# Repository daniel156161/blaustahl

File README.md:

# Blaustahl Storage Device

The Blaustahl USB dongle provides long-term storage for about 8000 characters of text. Simply plug the device into your computer and open any serial communications program that supports VT100 emulation (PuTTY, Tera Term, Minicom, screen, etc.) in order to access the built-in text editor.

This repo contains schematics, PCB layouts, firmware and a 3D-printable case.

Find usage instructions and more information on the [Blaustahl product page](https://machdyne.com/product/blaustahl-storage-device/).

## Connecting Blaustahl

The following sections will describe how to connect to Blaustahl on different operating systems. Once you're connected, press CTRL-G to view the on-device help screen.

### Linux

1. Install screen or minicom:

```
$ sudo apt install screen
$ sudo apt install minicom
```

2. After plugging in Blaustahl, find the device:

```
$ dmesg | grep ACM
```

3. Connect to the device (for example):

```
$ screen /dev/ttyACM0
or
$ minicom -D /dev/ttyACM0
```

If the device is already plugged in and you see nothing, you may need to press CTRL-L to refresh the display.

### OS X

1. Open the Terminal application.

2. After plugging in Blaustahl, find the device:

```
$ ls /dev/tty.usbmodem*
```

3. Connect to the device (for example):

```
$ screen /dev/tty.usbmodem1234561
```

### Windows

1. Download and install [PuTTY](https://www.chiark.greenend.org.uk/~sgtatham/putty/latest.html).

2. After plugging in Blaustahl, find the device by opening Device Manager and looking under "Ports (COM & LPT)" for "USB Serial Device (COMx)".

3. Open PuTTY and set connection type to Serial. Enter COMx (e.g. COM4) in the serial line box and press the Open button.

### Nix Flake Support

For users who prefer Nix, a [Nix Flake](https://nixos.wiki/wiki/Flakes) is now available to simplify building and using Blaustahl's firmware and utility tools. This section offers an alternative method that does not replace the existing instructions for non-Nix environments.

#### Prerequisites:
- Install [Nix](https://nixos.org/download) and enable flake support by adding `experimental-features = nix-command flakes` to your Nix configuration.

#### Building with the Flake:

Instead of cloning the repository manually, you can reference the flake directly using its GitHub address.

1. Use the flake to build the firmware, `bs` utility, or `srwp` tool:

    - To build and obtain the firmware files:
      ```bash
      nix build github:machdyne/blaustahl#firmware
      ```
      The UF2 files will be placed in `result/lib/firmware/`.

    - To build the `bs` utility:
      ```bash
      nix build github:machdyne/blaustahl#bs
      ```
      The binary will be available in the Nix store, with a symlink at `result/bin/bs`.

    - To build the `srwp` tool:
      ```bash
      nix build github:machdyne/blaustahl#srwp
      ```
      Similarly, you'll find the resulting script or binary under `result/bin/srwp`.

**Note:**
- These steps are optional for those using Nix and do not affect the regular installation and usage instructions provided above for other environments.

## Using Blaustahl

Blaustahl includes a built-in text editor with four 80x24 pages of text. The cursor can be moved with the arrow keys. When you'd like to enter or delete text, press CTRL-W to toggle the write mode.

| Keypress | Action |
| -------- | ------ |
| CTRL-G | Help |
| CTRL-L | Refresh screen |
| CTRL-W | Toggle write mode |
| CTRL-S | Toggle status bar |
| CTRL-Y | Enter firmware update mode |
| PGUP/DN | Navigate between pages |
| CTRL-A or ^ | Move to beginning of line |
| CTRL-E or $ | Move to end of line |

## Software

The 'bs' utility program can be used to read and write the FRAM data. Note that it's not possible to use this utility with the cdconly firmware, please install the composite firmware (blaustahl-x.x.x.uf2) in order to use the `bs` utility.

Build and install:

If using OS X:
```
$ brew install libusb
```

If using Linux:
```
$ sudo apt install libusb-1.0-0-dev
```

Then:

```
$ cd sw
$ make
$ sudo make install
$ sudo bs -r my-backup.bin
```
## API

To read or write data to FRAM memory via software, use the built-in API Simple Read Write Protocol (SRWP). An example and description of the protocol can be found in this [repository](https://github.com/binqbit/serialport_srwp).

See `sw/srwp.py` for an SRWP example using Python.

## Firmware

The [firmware](firmware) can be updated over USB by pressing CTRL-Y in the text editor to enter the UF2 bootloader mode. You can also enter the bootloader by holding the button while plugging in the device.

Once in bootloader mode, you can update the firmware by dragging and dropping a new UF2 file to the device.

There are two firmware images available:

  * blaustahl-x.x.x.uf2: USB composite device with USB-CDC and vendor interface
  * blaustahl\_cdconly-x.x.x.uf2: USB-CDC simple device

Blaustahl ships with `ship/blaustahl\_cdconly.uf2` installed.

The vendor interface allows you to access the 'bs' utility and to develop custom
software that interfaces with Blaustahl.

You can build the firmware from source, if you have [pico-sdk](https://github.com/raspberrypi/pico-sdk) installed:

```
$ cd firmware/blaustahl
$ mkdir build
$ cd build
$ cmake ..
$ make
```

## Future data recovery

In the event that the USB interface were to become obsolete or the RP2040 were to become non-functional, it should still be possible to recover the FRAM data using a SOP-8 test clip. The FRAM IC is marked "RS64".

One way to achieve this today is to load the Blaustahl firmware onto a Raspberry Pi Pico using the same SPI GPIOs as shown in the schematics, then hold the Blaustahl boot button while attaching a test clip to the FRAM IC. The text editor or 'bs' utility can then be used to recover the FRAM data.

## License

The contents of this repo are released under the [Lone Dynamics Open License](LICENSE.md).

Note: You can use these designs for commercial purposes but we ask that instead of producing exact clones, that you either replace our trademarks and logos with your own or add your own next to ours.

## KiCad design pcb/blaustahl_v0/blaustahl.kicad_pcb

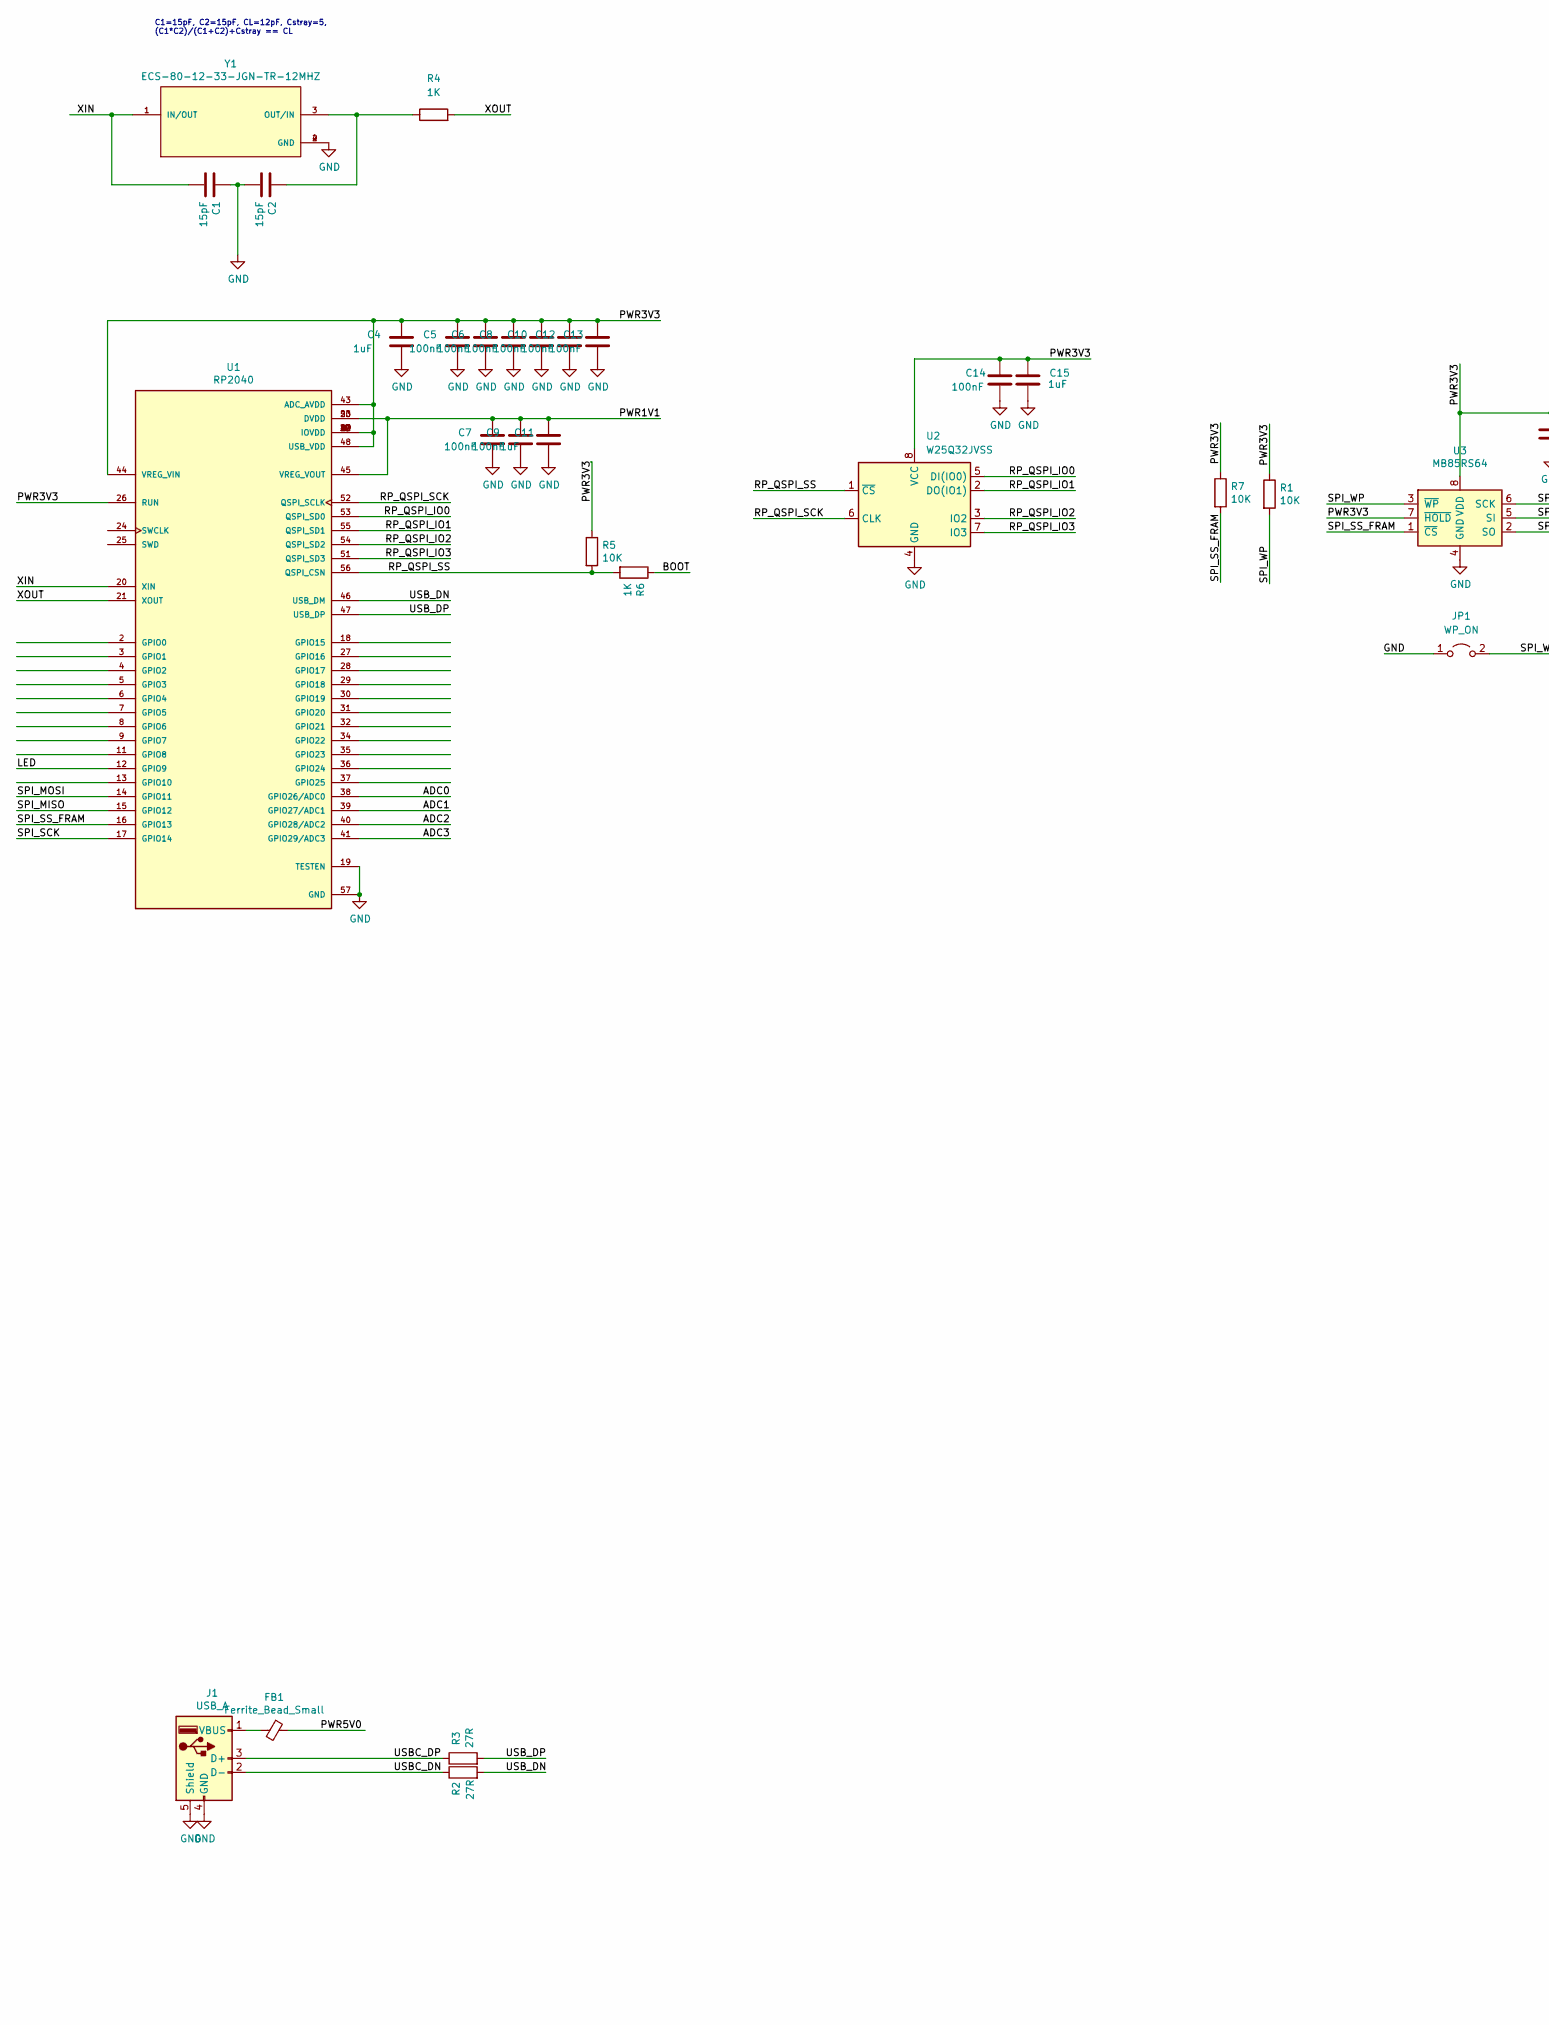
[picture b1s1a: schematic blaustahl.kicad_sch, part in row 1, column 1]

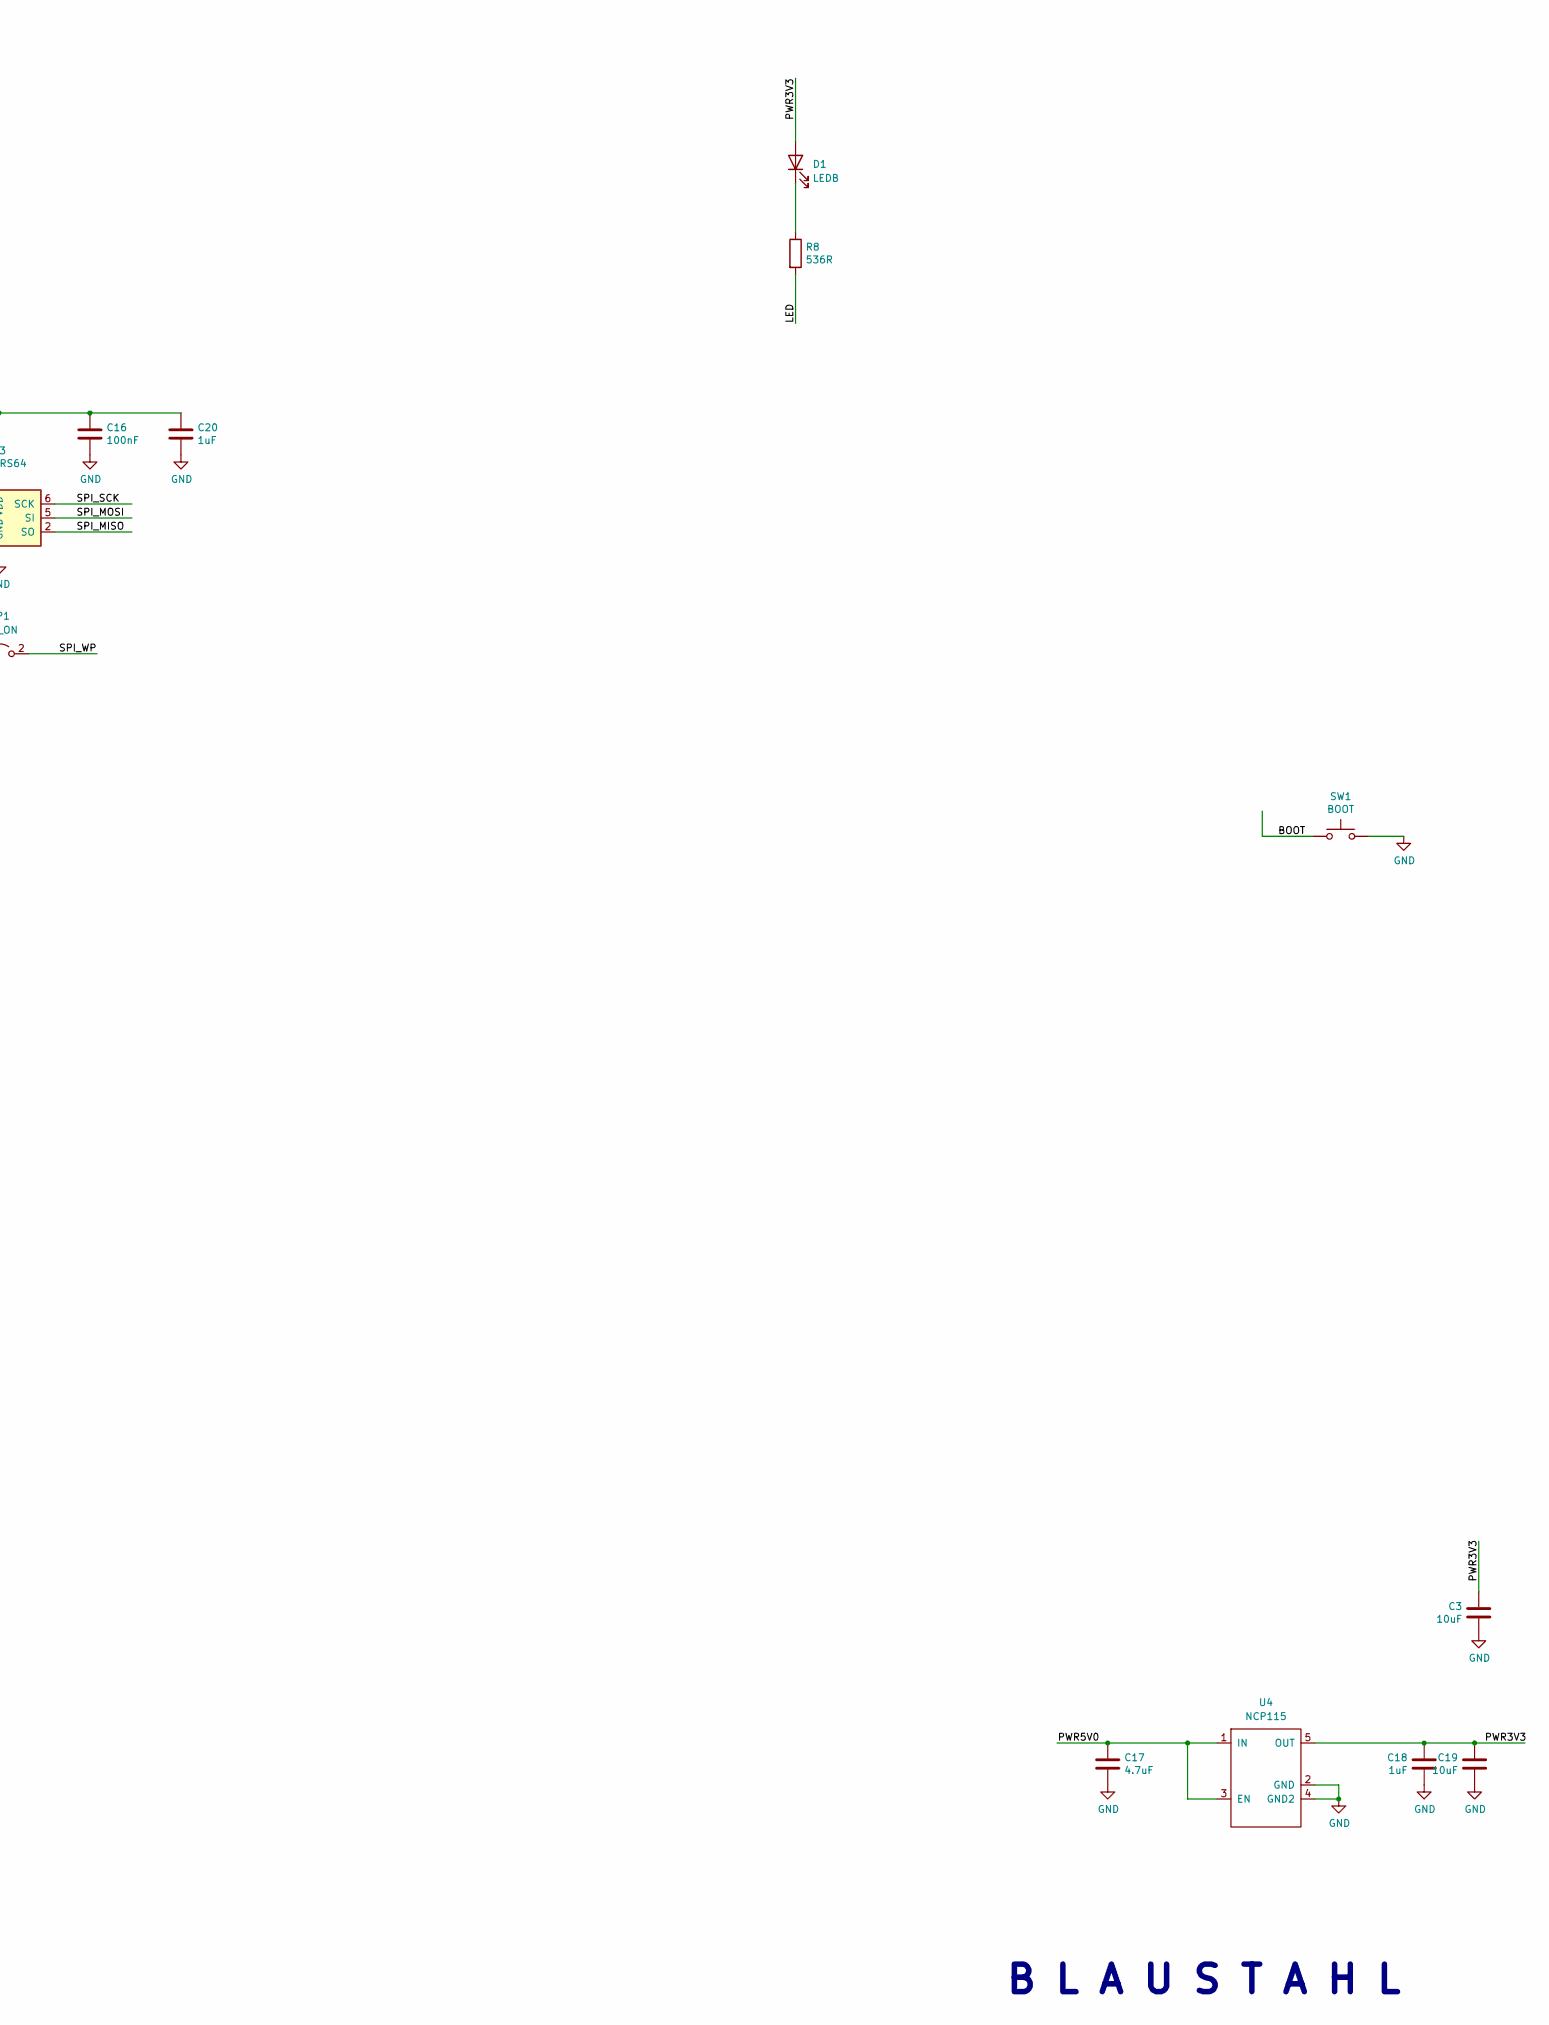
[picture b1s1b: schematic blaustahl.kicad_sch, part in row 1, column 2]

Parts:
C1, C2: 15pF; C_0402_1005Metric
C3, C19: 10uF; C_0402_1005Metric
C4, C11, C15, C18, C20: 1uF; C_0402_1005Metric
C5, C6, C7, C8, C9, C10, C12, C13, C14, C16: 100nF; C_0402_1005Metric
C17: 4.7uF; C_0402_1005Metric
D1: LEDB; LED_0603_1608Metric
FB1: Ferrite_Bead_Small; R_0402_1005Metric
J1: USB_A; USB_A_CNCTech_1001-011-01101_Horizontal
JP1: WP_ON; SolderJumper-2_P1.3mm_Open_Pad1.0x1.5mm
R1, R5, R7: 10K; R_0402_1005Metric
R2, R3: 27R; R_0402_1005Metric
R4, R6: 1K; R_0402_1005Metric
R8: 536R; R_0402_1005Metric
SW1: BOOT; Button_2P_3x4mm
U1: RP2040; RP2040-QFN-56-OFFICIAL; PARTREV 1.6.1
U2: W25Q32JVSS; SOIC-8_3.9x4.9mm_P1.27mm
U3: MB85RS64; SOIC-8_3.9x4.9mm_P1.27mm
U4: NCP115; TSOP-5_1.65x3.05mm_P0.95mm
Y1: ECS-80-12-33-JGN-TR-12MHZ; XTAL_ECS-240-8-33-AGN-TR

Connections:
/ADC0: U1.38 (GPIO26/ADC0)
/ADC1: U1.39 (GPIO27/ADC1)
/ADC2: U1.40 (GPIO28/ADC2)
/ADC3: U1.41 (GPIO29/ADC3)
/BOOT: R6.1, SW1.1
/LED: R8.2, U1.12 (GPIO9)
/PWR1V1: C7.1, C9.1, C11.1, U1.23 (DVDD), U1.45 (VREG_VOUT), U1.50 (DVDD)
/PWR3V3: C3.1, C4.1, C5.1, C6.1, C8.1, C10.1, C12.1, C13.1, C14.1, C15.1, C16.1, C18.1, C19.1, C20.1, D1.2 (A), R1.1, R5.1, R7.1, U1.1 (IOVDD), U1.10 (IOVDD), U1.22 (IOVDD), U1.26 (RUN), U1.33 (IOVDD), U1.42 (IOVDD), U1.43 (ADC_AVDD), U1.44 (VREG_VIN), U1.48 (USB_VDD), U1.49 (IOVDD), U2.8 (VCC), U3.7 (~HOLD), U3.8 (VDD), U4.5 (OUT)
/PWR5V0: C17.1, FB1.1, U4.1 (IN), U4.3 (EN)
/RP_QSPI_IO0: U1.53 (QSPI_SD0), U2.5 (DI(IO0))
/RP_QSPI_IO1: U1.55 (QSPI_SD1), U2.2 (DO(IO1))
/RP_QSPI_IO2: U1.54 (QSPI_SD2), U2.3 (IO2)
/RP_QSPI_IO3: U1.51 (QSPI_SD3), U2.7 (IO3)
/RP_QSPI_SCK: U1.52 (QSPI_SCLK), U2.6 (CLK)
/RP_QSPI_SS: R5.2, R6.2, U1.56 (QSPI_CSN), U2.1 (~CS)
/SPI_MISO: U1.15 (GPIO12), U3.2 (SO)
/SPI_MOSI: U1.14 (GPIO11), U3.5 (SI)
/SPI_SCK: U1.17 (GPIO14), U3.6 (SCK)
/SPI_SS_FRAM: R7.2, U1.16 (GPIO13), U3.1 (~CS)
/SPI_WP: JP1.2 (B), R1.2, U3.3 (~WP)
/USBC_DN: J1.2 (D-), R2.1
/USBC_DP: J1.3 (D+), R3.1
/USB_DN: R2.2, U1.46 (USB_DM)
/USB_DP: R3.2, U1.47 (USB_DP)
/XIN: C1.2, U1.20 (XIN), Y1.1 (IN/OUT)
/XOUT: R4.2, U1.21 (XOUT)
GND: C1.1, C2.2, C3.2, C4.2, C5.2, C6.2, C7.2, C8.2, C9.2, C10.2, C11.2, C12.2, C13.2, C14.2, C15.2, C16.2, C17.2, C18.2, C19.2, C20.2, J1.4 (GND), J1.5 (Shield), JP1.1 (A), SW1.2, U1.19 (TESTEN), U1.57 (GND), U2.4 (GND), U3.4 (GND), U4.2 (GND), U4.4 (GND2), Y1.2 (GND), Y1.4 (GND)
unnamed: C2.1, R4.1, Y1.3 (OUT/IN)
unnamed: D1.1 (K), R8.1
unnamed: FB1.2, J1.1 (VBUS)

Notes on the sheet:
C1=15pF, C2=15pF, CL=12pF, Cstray=5, (C1*C2)/(C1+C2)+Cstray == CL
B L A U S T A H L

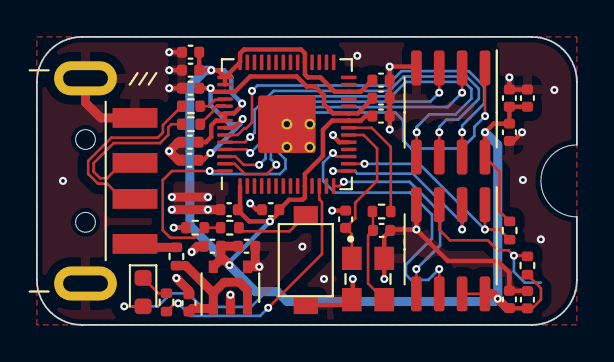
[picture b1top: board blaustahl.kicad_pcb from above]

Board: 2 copper layers, 30.0 x 16.0 mm, 38 parts (1 on the bottom side), 26 nets.

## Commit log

2025-06-25 add pcb
2025-06-25 improved printed error

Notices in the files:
pcb/blaustahl_v0/blaustahl.kicad_sch:
Copyright © 2024 Lone Dynamics Corporation
